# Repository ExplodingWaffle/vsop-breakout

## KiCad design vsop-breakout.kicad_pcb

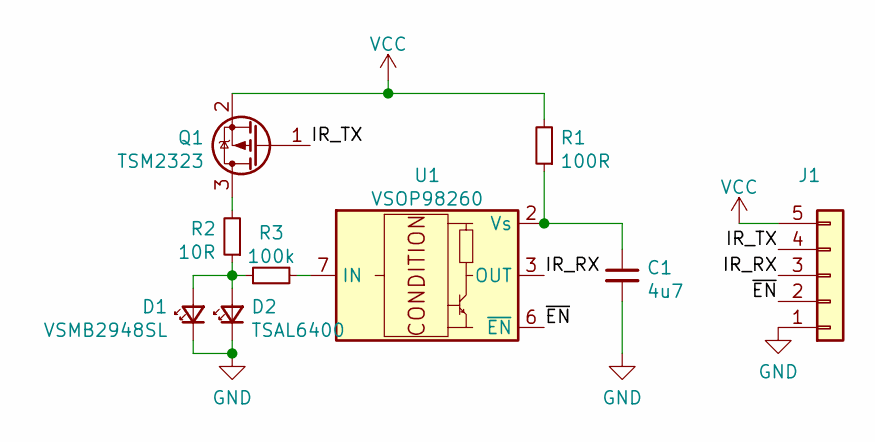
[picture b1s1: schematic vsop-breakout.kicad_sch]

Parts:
C1: 4u7; CAPC160X80X90L30
D1: VSMB2948SL; VISHAY_VSMB2948SL
D2: TSAL6400; LED_D5.0mm_Horizontal_O1.27mm_Z3.0mm_IRGrey
J1: PinHeader_1x05_P2.54mm_Vertical
Q1: TSM2323; SOT23-3P95_237X112L50X40N
R1: 100R; RESC160X85X55L30
R2: 10R; RESC200X125X70L50
R3: 100k; RESC160X85X55L30
U1: VSOP98260; SON9P50_200X200X76L30X25T160X90N

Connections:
/IR_RX: J1.3, U1.3 (OUT)
/IR_TX: J1.4, Q1.1 (G)
GND: C1.2, D1.1 (K), D2.1 (K), J1.1
unnamed: C1.1, R1.1, U1.2 (Vs)
unnamed: D1.2 (A), D2.2 (A), R2.1, R3.1
unnamed: Q1.3 (D), R2.2
unnamed: R3.2, U1.7 (IN)
VCC: J1.5, Q1.2 (S), R1.2
~EN: J1.2, U1.6 (~EN), U1.8 (~EN), U1.9 (~EN)

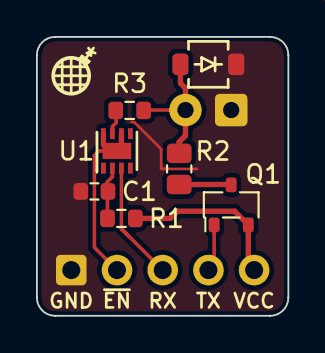
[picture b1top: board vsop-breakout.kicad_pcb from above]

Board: 2 copper layers, 14.0 x 15.5 mm, 9 parts (1 on the bottom side), 9 nets.
